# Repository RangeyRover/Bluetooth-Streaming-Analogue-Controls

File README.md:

# Bluetooth-Streaming-Analogue-Controls
Bluetooth streaming module developed for a Land Rover CD400 for a Discovery 3. Will work with any Car Stereo with analogue steering controls (Resistive) where the ADC supply is not above 5V 

Arduino Code
/*
  Bluetooth CD400 Streaming

 Reads an analogue input from steering controls and changes tracks on a bluetooth module using
 an arduino interface to the bluetooth streaming Module

  The circuit:
   created 2019
  by RangeyRover

  This example code is in the public domain.

*/

// constants won't change. Used here to set a pin number:
const int SkipLeftPin = 0 ;// the number of the Skip Left pin
const int SkipRightPin = 1 ;// the number of the Skip Right pin
const int VolUpPin = 2 ;// the number of the Vol up pin
const int VolDownPin = 3 ;// the number of the Vol Down pin
const int PlayPin = 4 ;// the number of the Play/Pause pin

// Variables will change:

int SkipLeftState = LOW;        // SkipLeftState used to set the Skip Left pin
int SkipRightState = LOW;        // SkipRightState used to set the Skip Right pin
int VolUpState = LOW;        // VolUpState used to set the Vol Up pin
int VolDownState = LOW;        // VolDownState used to set the Vol Down pin
int PlayPinState = 0;        // VolDownState used to set the Vol Down pin

// Generally, you should use "unsigned long" for variables that hold time
// The value will quickly become too large for an int to store
unsigned long previousMillis = 0;        // will store last time LED was updated

// constants won't change:
const long interval = 1000;           // interval at which to blink (milliseconds)

void setup() {
  // set the digital pins as output:
  pinMode(SkipLeftPin, OUTPUT);
  pinMode(SkipRightPin, OUTPUT);
  Serial.begin(9600);
}

void loop() {
  // here is where you'd put code that needs to be running all the time.

  // check to see if it's time to blink the LED; that is, if the difference
  // between the current time and last time you blinked the LED is bigger than
  // the interval at which you want to blink the LED.
  unsigned long currentMillis = millis();

  // read the input on analog pin 0:
  int sensorValue = analogRead(A0);
  // print out the value you read:
  Serial.println(sensorValue);
  delay(5);        // delay in between reads for stability
  // Determine which Key has pressed on analog pin 0
  // D3 Steering controls 5 Keys. Mode Range 200-260 Vol Up 500-560 Vol Down 0-80 Skip left 360-420 Skip Right 460-520
  if (currentMillis - previousMillis >= interval) {
     digitalWrite(PlayPin, HIGH);
     PlayPinState = 1;
  }
  else {
    digitalWrite(PlayPin, LOW);
    PlayPinState = 0;
  }
  if (sensorValue > 360 && sensorValue < 420) {
    digitalWrite(SkipLeftPin, HIGH);
  } else {
    digitalWrite(SkipLeftPin, LOW);
     }
  if (sensorValue > 460 && sensorValue < 520) {
    digitalWrite(SkipRightPin, HIGH);
  } else {
    digitalWrite(SkipRightPin, LOW);
  }
  delay(1);        // delay in between reads for stability
}

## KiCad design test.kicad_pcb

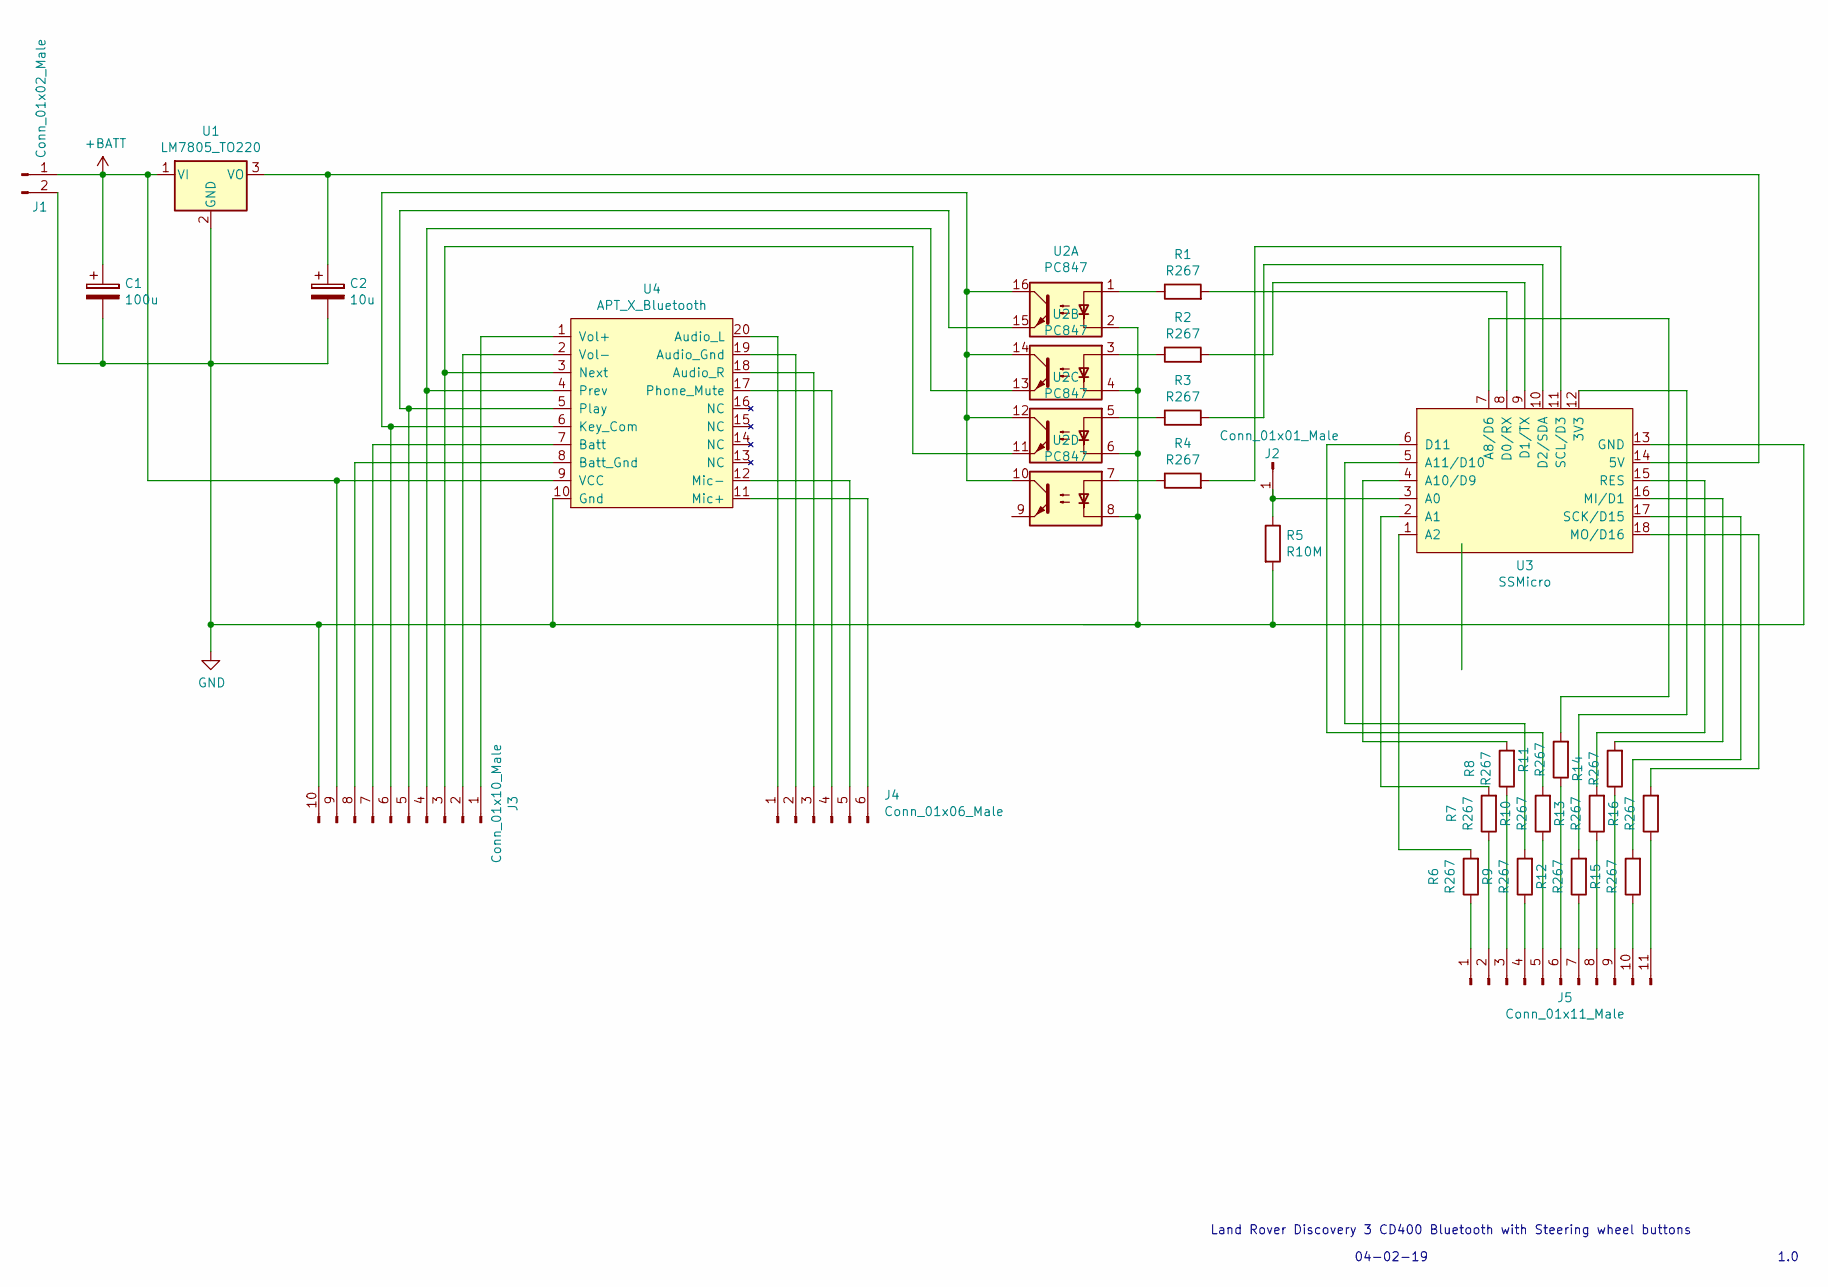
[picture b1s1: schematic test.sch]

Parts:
C1: 100u; CP_Radial_D8.0mm_P3.80mm
C2: 10u; CP_Radial_D8.0mm_P3.80mm
J1: Conn_01x02_Male; PinHeader_1x02_P2.54mm_Vertical
J2: Conn_01x01_Male; PinHeader_1x01_P2.54mm_Vertical
J3: Conn_01x10_Male; PinHeader_1x10_P2.54mm_Vertical
J4: Conn_01x06_Male; PinHeader_1x06_P2.54mm_Vertical
J5: Conn_01x11_Male; PinHeader_1x11_P2.54mm_Vertical
R1, R2, R3, R4, R6, R7, R8, R9, R10, R11, R12, R13, R14, R15, R16: R267; R_Axial_DIN0204_L3.6mm_D1.6mm_P5.08mm_Horizontal
R5: R10M; R_Axial_DIN0204_L3.6mm_D1.6mm_P5.08mm_Horizontal
U1: LM7805_TO220; TO-220-3_Vertical
U2: PC847; DIP-16_W7.62mm
U3: SSMicro; SS_Micro
U4: APT_X_Bluetooth; DIP-20_1200_ELL

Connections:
+BATT: C1.1, J1.1, J3.9, U1.1 (VI), U4.9 (VCC)
GND: C1.2, C2.2, J1.2, J3.10, R5.2, U1.2 (GND), U2.2, U2.4, U2.6, U2.8, U3.13 (GND), U4.10 (Gnd)
unnamed: C2.1, U1.3 (VO), U3.14 (5V)
unnamed: J2.1, R5.1, U3.3 (A0)
unnamed: J3.1, U4.1 (Vol+)
unnamed: J3.2, U4.2 (Vol-)
unnamed: J3.3, U2.11, U4.3 (Next)
unnamed: J3.4, U2.13, U4.4 (Prev)
unnamed: J3.5, U2.15, U4.5 (Play)
unnamed: J3.6, U2.10, U2.12, U2.14, U2.16, U4.6 (Key_Com)
unnamed: J3.7, U4.7 (Batt)
unnamed: J3.8, U4.8 (Batt_Gnd)
unnamed: J4.1, U4.20 (Audio_L)
unnamed: J4.2, U4.19 (Audio_Gnd)
unnamed: J4.3, U4.18 (Audio_R)
unnamed: J4.4, U4.17 (Phone_Mute)
unnamed: J4.5, U4.12 (Mic-)
unnamed: J4.6, U4.11 (Mic+)
unnamed: J5.1, R6.1
unnamed: J5.2, R7.1
unnamed: J5.3, R8.1
unnamed: J5.4, R9.1
unnamed: J5.5, R10.1
unnamed: J5.6, R11.1
unnamed: J5.7, R12.1
unnamed: J5.8, R13.1
unnamed: J5.9, R14.1
unnamed: J5.10, R15.1
unnamed: J5.11, R16.1
unnamed: R1.1, U2.1
unnamed: R1.2, U3.8 (D0/RX)
unnamed: R2.1, U2.3
unnamed: R2.2, U3.9 (D1/TX)
unnamed: R3.1, U2.5
unnamed: R3.2, U3.10 (D2/SDA)
unnamed: R4.1, U2.7
unnamed: R4.2, U3.11 (SCL/D3)
unnamed: R6.2, U3.1 (A2)
unnamed: R7.2, U3.2 (A1)
unnamed: R8.2, U3.4 (A10/D9)
unnamed: R9.2, U3.5 (A11/D10)
unnamed: R10.2, U3.6 (D11)
unnamed: R11.2, U3.7 (A8/D6)
unnamed: R12.2, U3.12 (3V3)
unnamed: R13.2, U3.15 (RES)
unnamed: R14.2, U3.16 (MI/D1)
unnamed: R15.2, U3.17 (SCK/D15)
unnamed: R16.2, U3.18 (MO/D16)

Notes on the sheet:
Land Rover Discovery 3 CD400 Bluetooth with Steering wheel buttons
04-02-19
1.0

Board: 2 copper layers, 27 parts (12 on the bottom side), 48 nets, no tracks yet.

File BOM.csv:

Source:,,,,,
Date:,09/03/2019 15:12,,,,
Tool:,Eeschema (5.0.2)-1,,,,
Component Count:,27,,,,
Ref,Value,Footprint,Datasheet,Manufacturer,Vendor
C1,100u,Capacitor_THT:CP_Radial_D8.0mm_P3.80mm,~,,
C2,10u,Capacitor_THT:CP_Radial_D8.0mm_P3.80mm,~,,
J1,Conn_01x02_Male,Connector_PinHeader_2.54mm:PinHeader_1x02_P2.54mm_Vertical,~,,
J2,Conn_01x01_Male,Connector_PinHeader_2.54mm:PinHeader_1x01_P2.54mm_Vertical,~,,
J3,Conn_01x10_Male,Connector_PinHeader_2.54mm:PinHeader_1x10_P2.54mm_Vertical,~,,
J4,Conn_01x06_Male,Connector_PinHeader_2.54mm:PinHeader_1x06_P2.54mm_Vertical,~,,
J5,Conn_01x11_Male,Connector_PinHeader_2.54mm:PinHeader_1x11_P2.54mm_Vertical,~,,
R1,R267,Resistor_THT:R_Axial_DIN0204_L3.6mm_D1.6mm_P5.08mm_Horizontal,~,,
R2,R267,Resistor_THT:R_Axial_DIN0204_L3.6mm_D1.6mm_P5.08mm_Horizontal,~,,
R3,R267,Resistor_THT:R_Axial_DIN0204_L3.6mm_D1.6mm_P5.08mm_Horizontal,~,,
R4,R267,Resistor_THT:R_Axial_DIN0204_L3.6mm_D1.6mm_P5.08mm_Horizontal,~,,
R5,R10M,Resistor_THT:R_Axial_DIN0204_L3.6mm_D1.6mm_P5.08mm_Horizontal,~,,
R6,R267,Resistor_THT:R_Axial_DIN0204_L3.6mm_D1.6mm_P5.08mm_Horizontal,~,,
R7,R267,Resistor_THT:R_Axial_DIN0204_L3.6mm_D1.6mm_P5.08mm_Horizontal,~,,
R8,R267,Resistor_THT:R_Axial_DIN0204_L3.6mm_D1.6mm_P5.08mm_Horizontal,~,,
R9,R267,Resistor_THT:R_Axial_DIN0204_L3.6mm_D1.6mm_P5.08mm_Horizontal,~,,
R10,R267,Resistor_THT:R_Axial_DIN0204_L3.6mm_D1.6mm_P5.08mm_Horizontal,~,,
R11,R267,Resistor_THT:R_Axial_DIN0204_L3.6mm_D1.6mm_P5.08mm_Horizontal,~,,
R12,R267,Resistor_THT:R_Axial_DIN0204_L3.6mm_D1.6mm_P5.08mm_Horizontal,~,,
R13,R267,Resistor_THT:R_Axial_DIN0204_L3.6mm_D1.6mm_P5.08mm_Horizontal,~,,
R14,R267,Resistor_THT:R_Axial_DIN0204_L3.6mm_D1.6mm_P5.08mm_Horizontal,~,,
R15,R267,Resistor_THT:R_Axial_DIN0204_L3.6mm_D1.6mm_P5.08mm_Horizontal,~,,
R16,R267,Resistor_THT:R_Axial_DIN0204_L3.6mm_D1.6mm_P5.08mm_Horizontal,~,,
U1,LM7805_TO220,Package_TO_SOT_THT:TO-220-3_Vertical,http://www.fairchildsemi.com/ds/LM/LM7805.pdf,,
U2,PC847,Package_DIP:DIP-16_W7.62mm,http://www.soselectronic.cz/a_info/resource/d/pc817.pdf,,
U3,SSMicro,SS_Micro:SS_Micro,,,"https://www.aliexpress.com/item/Free-shipping-SS-micro-ATMEG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,searchweb201602_3_10065_10068_10130_10547_319_317_10548_10696_453_10084_454_10083_10618_10307_537_536_10131_10132_10902_10133_10059_10884_10887_321_322_10103,searchweb201603_6,ppcSwitch_0&algo_expid=89283a5d-8a84-4d8a-aa21-38fdb3e2278e-0&algo_pvid=89283a5d-8a84-4d8a-aa21-38fdb3e2278e"
U4,APT_X_Bluetooth,SS_Micro:DIP-20_1200_ELL,,,"https://www.aliexpress.com/item/CSR8645-APT-X-HIFI-Bluetooth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,searchweb201602_3_10065_10068_10130_10547_319_317_10548_10696_453_10084_454_10083_10618_10307_537_536_10131_10132_10902_10133_10059_10884_10887_321_322_10103,searchweb201603_6,ppcSwitch_0&algo_expid=eede32d0-7e69-428b-86b3-611ed77cad83-3&algo_pvid=eede32d0-7e69-428b-86b3-611ed77cad83"

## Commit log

2019-03-09 Add files via upload
    Circuit Schematic
2019-03-09 Add files via upload
    Bill of materials
